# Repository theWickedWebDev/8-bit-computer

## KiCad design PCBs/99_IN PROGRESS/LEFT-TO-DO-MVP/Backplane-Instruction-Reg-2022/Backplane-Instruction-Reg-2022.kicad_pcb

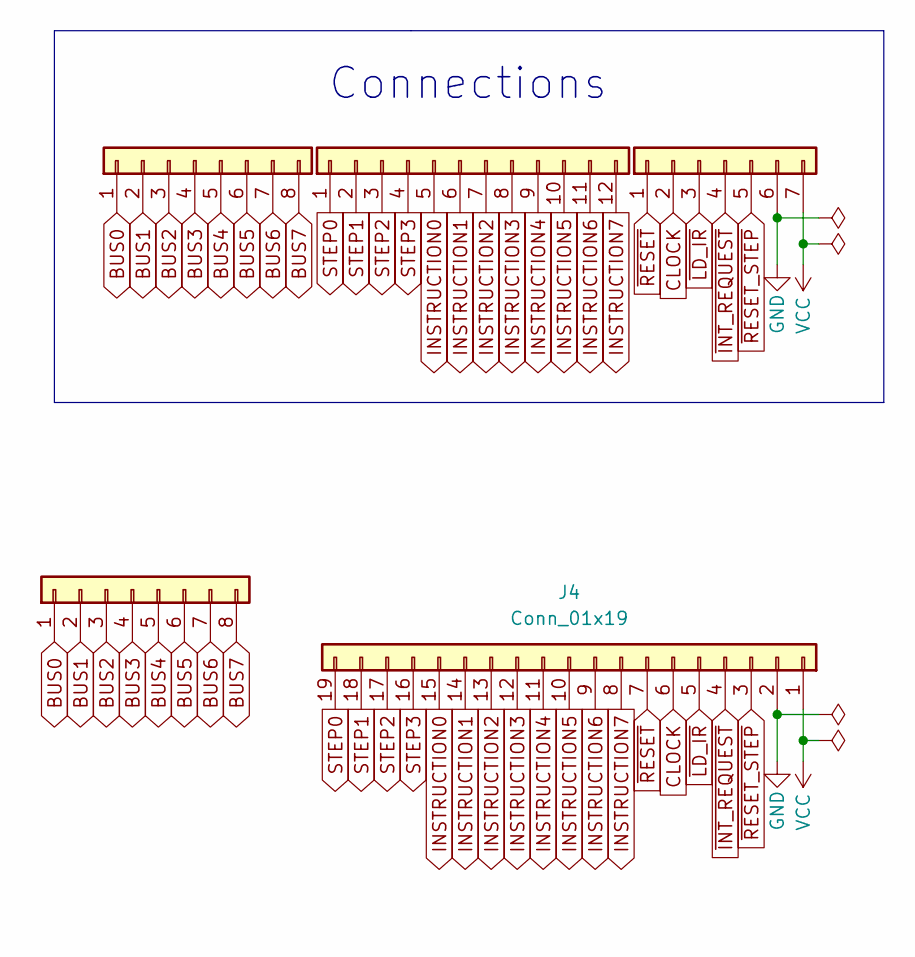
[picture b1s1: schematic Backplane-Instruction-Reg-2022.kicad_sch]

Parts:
J1: Conn_01x08; PinHeader_1x08_P2.54mm_Vertical
J2: Conn_01x08; PinSocket_1x08_P2.54mm_Vertical
J3: Conn_01x12; PinSocket_1x12_P2.54mm_Vertical
J4: Conn_01x19; PinHeader_1x19_P2.54mm_Horizontal
J5: Conn_01x07; PinSocket_1x07_P2.54mm_Vertical

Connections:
BUS0: J1.1, J2.1
BUS1: J1.2, J2.2
BUS2: J1.3, J2.3
BUS3: J1.4, J2.4
BUS4: J1.5, J2.5
BUS5: J1.6, J2.6
BUS6: J1.7, J2.7
BUS7: J1.8, J2.8
CLOCK: J4.6, J5.2
GND: J4.2, J5.6
INSTRUCTION0: J3.5, J4.15
INSTRUCTION1: J3.6, J4.14
INSTRUCTION2: J3.7, J4.13
INSTRUCTION3: J3.8, J4.12
INSTRUCTION4: J3.9, J4.11
INSTRUCTION5: J3.10, J4.10
INSTRUCTION6: J3.11, J4.9
INSTRUCTION7: J3.12, J4.8
STEP0: J3.1, J4.19
STEP1: J3.2, J4.18
STEP2: J3.3, J4.17
STEP3: J3.4, J4.16
VCC: J4.1, J5.7
~INT_REQUEST: J4.4, J5.4
~LD_IR: J4.5, J5.3
~RESET_STEP: J4.3, J5.5
~RESET: J4.7, J5.1

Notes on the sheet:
Connections

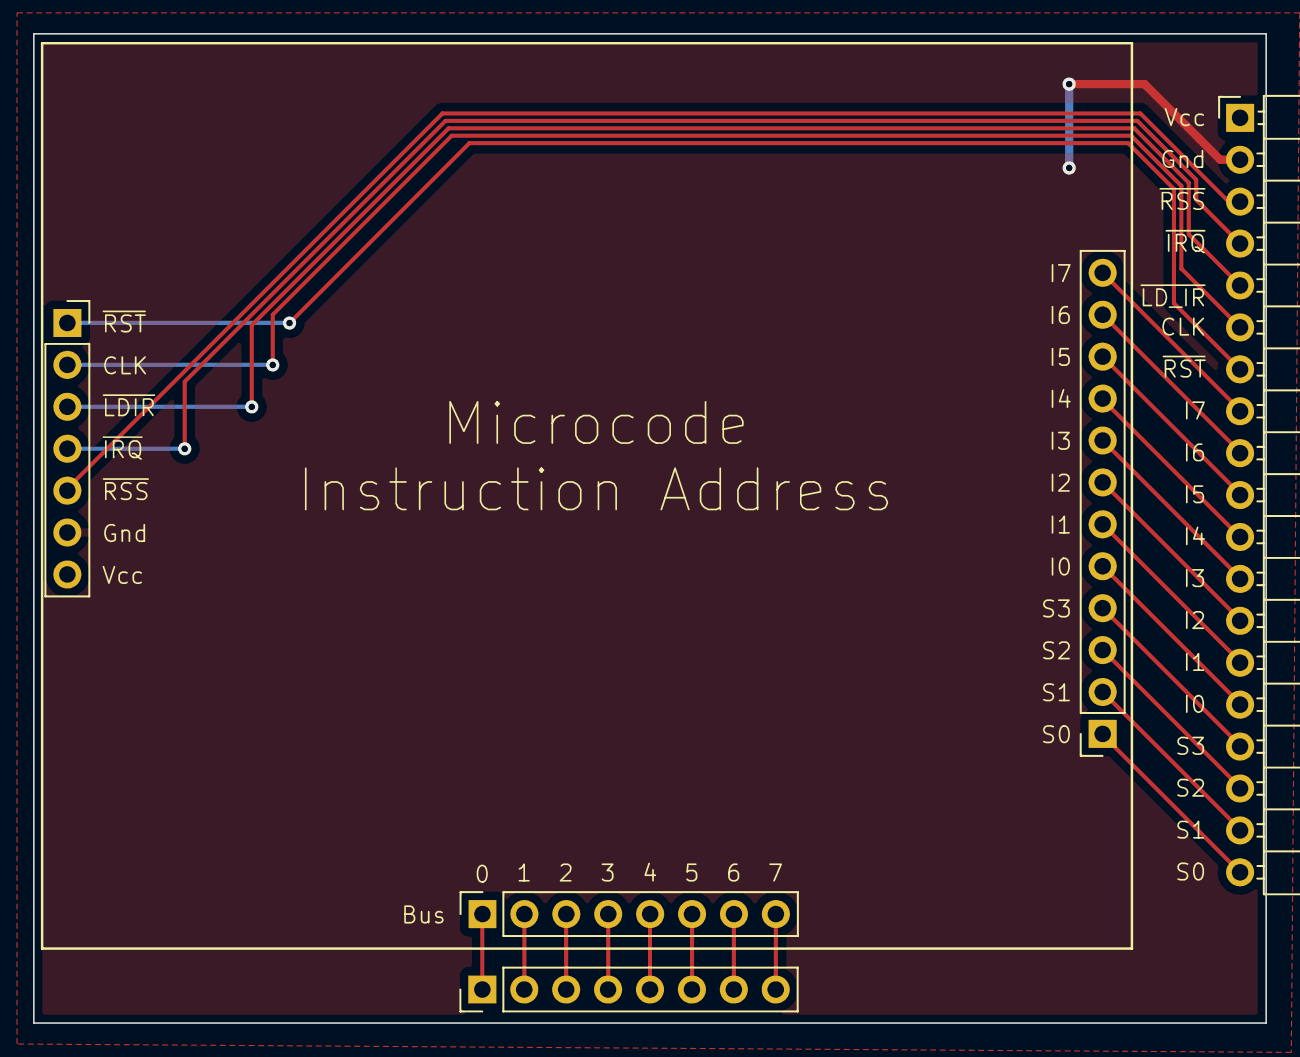
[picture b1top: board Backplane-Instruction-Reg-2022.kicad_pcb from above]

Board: 2 copper layers, 74.7 x 59.9 mm, 5 parts (0 on the bottom side), 27 nets.

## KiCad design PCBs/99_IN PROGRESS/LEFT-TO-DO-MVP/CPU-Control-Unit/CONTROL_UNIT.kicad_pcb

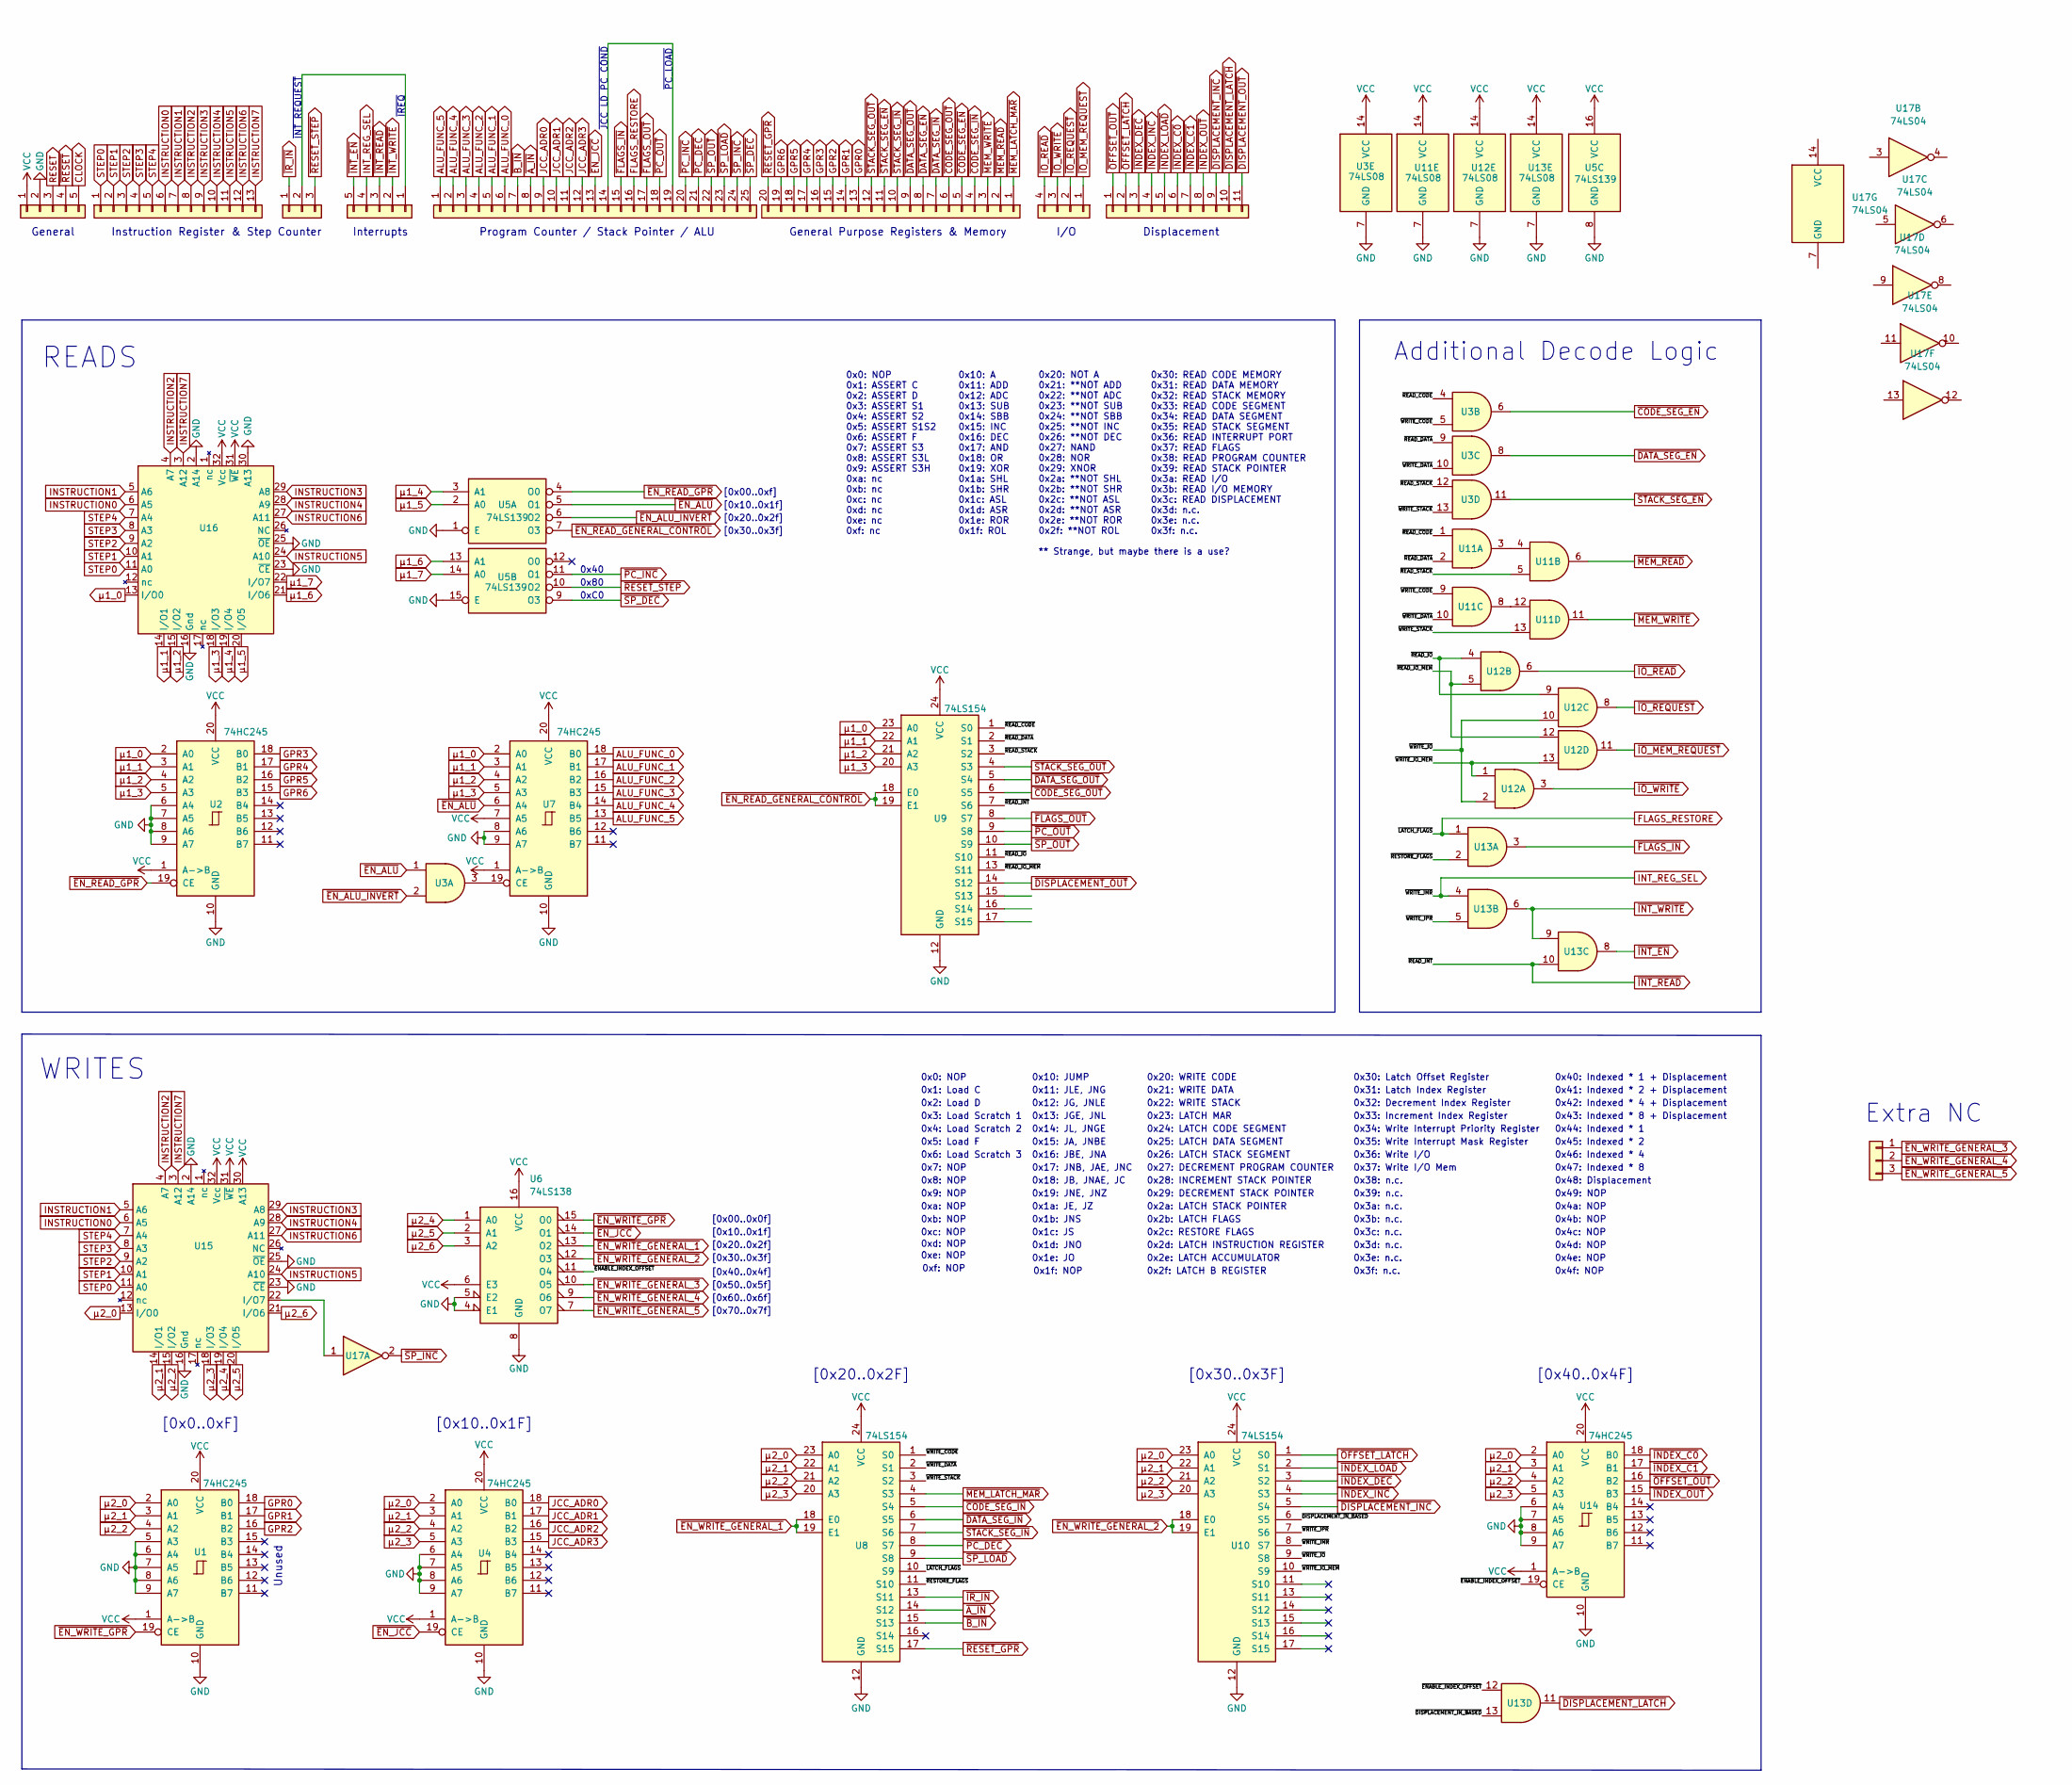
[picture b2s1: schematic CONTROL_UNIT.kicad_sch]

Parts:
J1, J4: Conn_01x05; PinHeader_1x05_P2.54mm_Vertical
J2: Conn_01x13; PinHeader_1x13_P2.54mm_Vertical
J3, J9: Conn_01x03; PinHeader_1x03_P2.54mm_Vertical
J5: Conn_01x25; PinHeader_1x25_P2.54mm_Vertical
J6: Conn_01x20; PinHeader_1x20_P2.54mm_Vertical
J7: Conn_01x04; PinHeader_1x04_P2.54mm_Vertical
J8: Conn_01x10; PinHeader_1x11_P2.54mm_Vertical
U1, U2, U4, U7, U14: 74HC245; SOIC-20W_7.5x12.8mm_P1.27mm
U3, U11, U12, U13: 74LS08; SOIC-14_3.9x8.7mm_P1.27mm
U5: 74LS139; SOIC-16_3.9x9.9mm_P1.27mm
U6: 74LS138; SOIC-16_3.9x9.9mm_P1.27mm
U8, U9, U10: 74LS154; SOIC-24W_7.5x15.4mm_P1.27mm
U15, U16: PLCC32_28_28C256; Socket-PLCC-32
U17: 74LS04

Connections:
/~DISPLACEMENT_IN_BASED: U10.6 (S5), U13.13
/~ENABLE_INDEX_OFFSET: U6.11 (O4), U13.12, U14.19 (CE)
/~READ_CODE: U3.4, U9.1 (S0), U11.1
/~READ_DATA: U3.9, U9.2 (S1), U11.2
/~READ_IO_MEM: U9.13 (S11), U12.5, U12.12
/~READ_IO: U9.11 (S10), U12.4, U12.9
/~READ_STACK: U3.12, U9.3 (S2), U11.5
/~RESTORE_FLAGS: U8.11 (S10), U13.2
/~WRITE_CODE: U3.5, U8.1 (S0), U11.9
/~WRITE_DATA: U3.10, U8.2 (S1), U11.10
/~WRITE_IO_MEM: U10.10 (S9), U12.1, U12.13
/~WRITE_IO: U10.9 (S8), U12.2, U12.10
/~WRITE_IPR: U10.7 (S6), U13.5
/~WRITE_STACK: U3.13, U8.3 (S2), U11.13
ALU_FUNC_0: J5.6, U7.18 (B0)
ALU_FUNC_1: J5.5, U7.17 (B1)
ALU_FUNC_2: J5.4, U7.16 (B2)
ALU_FUNC_3: J5.3, U7.15 (B3)
ALU_FUNC_4: J5.2, U7.14 (B4)
ALU_FUNC_5: J5.1, U7.13 (B5)
CLOCK: J1.5
FLAGS_RESTORE: J5.16, U8.10 (S9), U13.1
GND: J1.2, U1.5 (A3), U1.6 (A4), U1.7 (A5), U1.8 (A6), U1.9 (A7), U1.10 (GND), U2.6 (A4), U2.7 (A5), U2.8 (A6), U2.9 (A7), U2.10 (GND), U3.7 (GND), U4.6 (A4), U4.7 (A5), U4.8 (A6), U4.9 (A7), U4.10 (GND), U5.1 (E), U5.8 (GND), U5.15 (E), U6.4 (E1), U6.5 (E2), U6.8 (GND), U7.8 (A6), U7.9 (A7), U7.10 (GND), U8.12 (GND), U9.12 (GND), U10.12 (GND), U11.7 (GND), U12.7 (GND), U13.7 (GND), U14.6 (A4), U14.7 (A5), U14.8 (A6), U14.9 (A7), U14.10 (GND), U15.2 (A14), U15.16 (Gnd), U15.23 (~CE), U15.25 (~OE), U16.2 (A14), U16.16 (Gnd), U16.23 (~CE), U16.25 (~OE), U16.30 (A13)
GPR0: J6.13, U1.18 (B0)
GPR1: J6.14, U1.17 (B1)
GPR2: J6.15, U1.16 (B2)
GPR3: J6.16, U2.18 (B0)
GPR4: J6.17, U2.17 (B1)
GPR5: J6.18, U2.16 (B2)
GPR6: J6.19, U2.15 (B3)
INSTRUCTION0: J2.6, U15.6 (A5), U16.6 (A5)
INSTRUCTION1: J2.7, U15.5 (A6), U16.5 (A6)
INSTRUCTION2: J2.8, U15.4 (A7), U16.4 (A7)
INSTRUCTION3: J2.9, U15.29 (A8), U16.29 (A8)
INSTRUCTION4: J2.10, U15.28 (A9), U16.28 (A9)
INSTRUCTION5: J2.11, U15.24 (A10), U16.24 (A10)
INSTRUCTION6: J2.12, U15.27 (A11), U16.27 (A11)
INSTRUCTION7: J2.13, U15.3 (A12), U16.3 (A12)
INT_REG_SEL: J4.4, U10.8 (S7), U13.4
JCC_ADR0: J5.9, U4.18 (B0)
JCC_ADR1: J5.10, U4.17 (B1)
JCC_ADR2: J5.11, U4.16 (B2)
JCC_ADR3: J5.12, U4.15 (B3)
unnamed: J3.2, J4.1
unnamed: J5.14, J5.19
unnamed: U3.3, U7.19 (CE)
unnamed: U11.3, U11.4
unnamed: U11.8, U11.12
unnamed: U15.22 (I/O7), U17.1
RESET: J1.3
STEP0: J2.1, U15.11 (A0), U16.11 (A0)
STEP1: J2.2, U15.10 (A1), U16.10 (A1)
STEP2: J2.3, U15.9 (A2), U16.9 (A2)
STEP3: J2.4, U15.8 (A3), U16.8 (A3)
STEP4: J2.5, U15.7 (A4), U16.7 (A4)
VCC: J1.1, U1.1 (A->B), U1.20 (VCC), U2.1 (A->B), U2.20 (VCC), U3.14 (VCC), U4.1 (A->B), U4.20 (VCC), U5.16 (VCC), U6.6 (E3), U6.16 (VCC), U7.1 (A->B), U7.7 (A5), U7.20 (VCC), U8.24 (VCC), U9.24 (VCC), U10.24 (VCC), U11.14 (VCC), U12.14 (VCC), U13.14 (VCC), U14.1 (A->B), U14.20 (VCC), U15.30 (A13), U15.31 (~WE), U15.32 (Vcc), U16.31 (~WE), U16.32 (Vcc)
~A_IN: J5.8, U8.14 (S12)
~B_IN: J5.7, U8.15 (S13)
~CODE_SEG_EN: J6.5, U3.6
~CODE_SEG_IN: J6.4, U8.5 (S4)
~CODE_SEG_OUT: J6.6, U9.6 (S5)
~DATA_SEG_EN: J6.8, U3.8
~DATA_SEG_IN: J6.7, U8.6 (S5)
~DATA_SEG_OUT: J6.9, U9.5 (S4)
~DISPLACEMENT_INC: J8.9, U10.5 (S4)
~DISPLACEMENT_LATCH: J8.10, U13.11
~DISPLACEMENT_OUT: J8.11, U9.14 (S12)
~EN_ALU_INVERT: U3.2, U5.6 (O2)
~EN_ALU: U3.1, U5.5 (O1), U7.6 (A4)
~EN_JCC: J5.13, U4.19 (CE), U6.14 (O1)
~EN_READ_GENERAL_CONTROL: U5.7 (O3), U9.18 (E0), U9.19 (E1)
~EN_READ_GPR: U2.19 (CE), U5.4 (O0)
~EN_WRITE_GENERAL_1: U6.13 (O2), U8.18 (E0), U8.19 (E1)
~EN_WRITE_GENERAL_2: U6.12 (O3), U10.18 (E0), U10.19 (E1)
~EN_WRITE_GENERAL_3: J9.1, U6.10 (O5)
~EN_WRITE_GENERAL_4: J9.2, U6.9 (O6)
~EN_WRITE_GENERAL_5: J9.3, U6.7 (O7)
~EN_WRITE_GPR: U1.19 (CE), U6.15 (O0)
~FLAGS_IN: J5.15, U13.3
~FLAGS_OUT: J5.17, U9.8 (S7)
~INDEX_C0: J8.6, U14.18 (B0)
~INDEX_C1: J8.7, U14.17 (B1)
~INDEX_DEC: J8.3, U10.3 (S2)
~INDEX_INC: J8.4, U10.4 (S3)
~INDEX_LOAD: J8.5, U10.2 (S1)
~INDEX_OUT: J8.8, U14.15 (B3)
~INT_EN: J4.5, U13.8
~INT_READ: J4.3, U9.7 (S6), U13.10
~INT_WRITE: J4.2, U13.6, U13.9
~IO_MEM_REQUEST: J7.1, U12.11
~IO_READ: J7.4, U12.6
~IO_REQUEST: J7.2, U12.8
~IO_WRITE: J7.3, U12.3
~IR_IN: J3.1, U8.13 (S11)
~MEM_LATCH_MAR: J6.1, U8.4 (S3)
~MEM_READ: J6.2, U11.6
~MEM_WRITE: J6.3, U11.11
~OFFSET_LATCH: J8.2, U10.1 (S0)
~OFFSET_OUT: J8.1, U14.16 (B2)
~PC_DEC: J5.21, U8.8 (S7)
~PC_INC: J5.20, U5.11 (O1)
~PC_OUT: J5.18, U9.9 (S8)
~RESET_GPR: J6.20, U8.17 (S15)
~RESET_STEP: J3.3, U5.10 (O2)
~RESET: J1.4
~SP_DEC: J5.25, U5.9 (O3)
~SP_INC: J5.24, U17.2
~SP_LOAD: J5.23, U8.9 (S8)
~SP_OUT: J5.22, U9.10 (S9)
~STACK_SEG_EN: J6.11, U3.11
~STACK_SEG_IN: J6.10, U8.7 (S6)
~STACK_SEG_OUT: J6.12, U9.4 (S3)
μ1_0: U2.2 (A0), U7.2 (A0), U9.23 (A0), U16.13 (I/O0)
μ1_1: U2.3 (A1), U7.3 (A1), U9.22 (A1), U16.14 (I/O1)
μ1_2: U2.4 (A2), U7.4 (A2), U9.21 (A2), U16.15 (I/O2)
μ1_3: U2.5 (A3), U7.5 (A3), U9.20 (A3), U16.18 (I/O3)
μ1_4: U5.3 (A1), U16.19 (I/O4)
μ1_5: U5.2 (A0), U16.20 (I/O5)
μ1_6: U5.13 (A1), U16.21 (I/O6)
μ1_7: U5.14 (A0), U16.22 (I/O7)
μ2_0: U1.2 (A0), U4.2 (A0), U8.23 (A0), U10.23 (A0), U14.2 (A0), U15.13 (I/O0)
μ2_1: U1.3 (A1), U4.3 (A1), U8.22 (A1), U10.22 (A1), U14.3 (A1), U15.14 (I/O1)
μ2_2: U1.4 (A2), U4.4 (A2), U8.21 (A2), U10.21 (A2), U14.4 (A2), U15.15 (I/O2)
μ2_3: U4.5 (A3), U8.20 (A3), U10.20 (A3), U14.5 (A3), U15.18 (I/O3)
μ2_4: U6.1 (A0), U15.19 (I/O4)
μ2_5: U6.2 (A1), U15.20 (I/O5)
μ2_6: U6.3 (A2), U15.21 (I/O6)

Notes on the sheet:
0x35: Write Interrupt Mask Register
Instruction Register
0x13: JGE, JNL
0x4a: NOP
0x3: Load Scratch 1
[0x30..0x3F]
[0x70..0x7f]
0x47: Indexed * 8
[0x20..0x2f]
0x3f: n.c.
0x17: JNB, JAE, JNC
0x6: Load Scratch 3
0xd: NOP
0x4c: NOP
Interrupts
0x12: JG, JNLE
[0x10..0x1f]
0x8: NOP
0x4f: NOP
0x37: Write I/O Mem
0x21: WRITE DATA
0x4b: NOP
[0x30..0x3f]
0x28: INCREMENT STACK POINTER
0x1c: JS
0xf: NOP
~{JCC_LD_PC_COND}
I/O
[0x40..0x4F]
0x3a: n.c.
0x41: Indexed * 2 + Displacement
0x14: JL, JNGE
WRITES
Program Counter / Stack Pointer / ALU
0x2e: LATCH ACCUMULATOR
0x2b: LATCH FLAGS
0x9: NOP
~{IREQ}
0x3e: n.c.
0x7: NOP

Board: 2 copper layers, 25 parts (8 on the bottom side), 122 nets, no tracks yet.

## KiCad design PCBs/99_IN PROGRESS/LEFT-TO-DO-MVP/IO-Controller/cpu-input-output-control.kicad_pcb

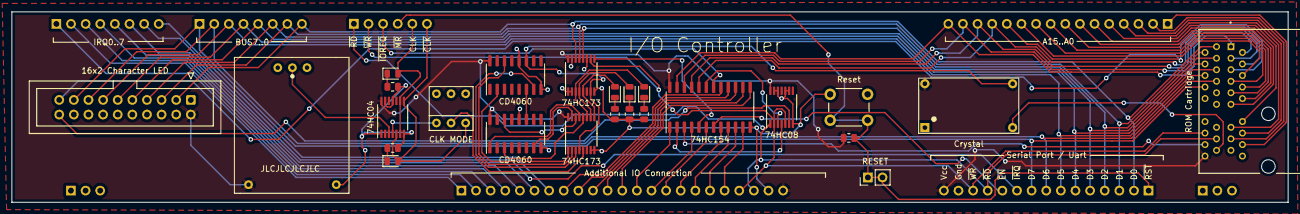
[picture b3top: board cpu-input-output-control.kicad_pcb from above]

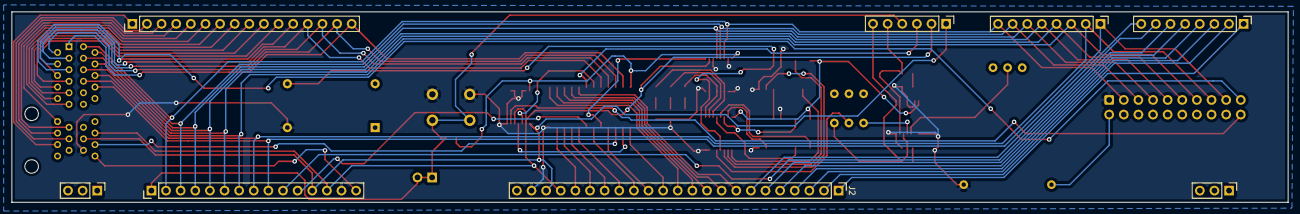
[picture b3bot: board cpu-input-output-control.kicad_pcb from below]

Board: 2 copper layers, 221.7 x 33.1 mm, 33 parts (8 on the bottom side), 78 nets.

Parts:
D1, D2, D3: LED; LED_RED_0805_2012Metric
D4, D5: LED; LED_BLUE_0805_2012Metric
J1: Conn_01x06; PinHeader_1x06_P2.54mm_Vertical
J2: Conn_01x23; PinHeader_1x23_P2.54mm_Vertical
J3: Conn_02x20_Odd_Even; IDC-Header_2x10_P2.54mm_Vertical
J4: Conn_01x02; PinHeader_1x02_P2.54mm_Vertical
J5: Conn_01x15; PinHeader_1x15_P2.54mm_Vertical
J6: Conn_01x16; PinHeader_1x16_P2.54mm_Vertical
J7, J8: Conn_01x03; PinHeader_1x03_P2.54mm_Vertical
J11, J16: Conn_01x08; PinHeader_1x08_P2.54mm_Vertical
J21: PCIE-036-02-X-D-RA; SAMTEC_PCIE-036-02-X-D-RA
R1, R2, R3, R4, R5, R6: R_Small_US; R_0805_2012Metric
SW1: SW_Push; SW_PUSH_6mm
SW2: SW_SPDT; THT-DPDT
U1: 74LS08; TSSOP-14_4.4x5mm_P0.65mm
U2: 74LS04; TSSOP-14_4.4x5mm_P0.65mm
U3: 74LS154; SO-24_5.3x15mm_P1.27mm
U4: debounced-btn; breakout-debounce-btn
U5, U8: CD4060; SOIC-16_3.9x9.9mm_P1.27mm
U6: 74LS173; TSSOP-16_4.4x5mm_P0.65mm
U7: 74LS251; TSSOP-16_4.4x5mm_P0.65mm
Y1: Crystal_GND24; DIP-14-4pin-clock

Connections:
/F0: D3.2 (A), U6.3 (Q0), U7.11 (S0)
/F1: D2.2 (A), U6.4 (Q1), U7.10 (S1)
/F2: D1.2 (A), U6.5 (Q2), U7.9 (S2)
A0: J6.16, J21.A01, U3.23 (A0)
A1: J6.15, J21.A02, U3.22 (A1)
A2: J6.14, J21.A03, U3.21 (A2)
A3: J6.13, J21.A04, U3.20 (A3)
A4: J3.19, J6.12, J21.A05
A5: J6.11, J21.A06
A6: J6.10, J21.A07
A7: J6.9, J21.A08
A8: J6.8, J21.A09
A9: J6.7, J21.A10
A10: J6.6, J21.A11
A11: J6.5, J21.A12
A12: J6.4, J21.A13
A13: J6.3, J21.A14
A14: J6.2, J21.A15
A15: J6.1, J21.A16
BUS0: J3.3, J5.2, J11.8, J21.B01, U6.14 (D0)
BUS1: J3.5, J5.3, J11.7, J21.B02, U6.13 (D1)
BUS2: J3.7, J5.4, J11.6, J21.B03, U6.12 (D2)
BUS3: J3.9, J5.5, J11.5, J21.B04
BUS4: J3.11, J5.6, J11.4, J21.B05
BUS5: J3.13, J5.7, J11.3, J21.B06
BUS6: J3.15, J5.8, J11.2, J21.B07
BUS7: J3.17, J5.9, J11.1, J21.B08
CLOCK: D4.2 (A), J1.5, U2.6, U2.9
CRYSTAL_CLOCK: U5.11 (I), U6.7 (Cp), U7.4 (I0), Y1.3
FREQ1: U5.7 (Q4), U7.3 (I1)
FREQ2: U5.14 (Q8), U7.2 (I2)
FREQ3: U5.2 (Q13), U7.1 (I3)
FREQ4: U7.15 (I4), U8.7 (Q4)
FREQ5: U7.14 (I5), U8.14 (Q8)
FREQ6: U7.13 (I6), U8.1 (Q12)
FREQ7: U7.12 (I7), U8.3 (Q14)
GND: J2.22, J3.1, J5.14, J21.B17, R2.2, R3.2, R4.2, R5.2, R6.2, SW1.1, U1.7 (GND), U1.9, U1.10, U1.12, U1.13, U2.1, U2.7 (GND), U2.11, U2.13, U3.12 (GND), U4.2 (Gnd), U5.8 (GND), U5.12 (RESET), U6.1 (Oe1), U6.2 (Oe2), U6.8 (GND), U6.11 (D3), U6.15 (Mr), U7.7 (~OE), U7.8 (GND), U8.8 (GND), U8.12 (RESET), Y1.2
MANUAL_CLOCK: U2.3, U4.3 (Q)
unnamed: D1.1 (K), R2.1
unnamed: D2.1 (K), R3.1
unnamed: D3.1 (K), R4.1
unnamed: D4.1 (K), R5.1
unnamed: D5.1 (K), R6.1
unnamed: J3.20, U1.6
unnamed: SW2.1 (A), U2.4
unnamed: SW2.3 (C), U7.5 (Y)
unnamed: U1.3, U3.19 (E1)
unnamed: U5.6 (Q7), U8.11 (I)
VCC: J2.23, J3.2, J5.15, J21.B18, R1.2, U1.14 (VCC), U2.14 (VCC), U3.24 (VCC), U4.1 (Vcc), U5.16 (VCC), U6.16 (VCC), U7.16 (VCC), U8.16 (VCC), Y1.4
~CLOCK: D5.2 (A), J1.6, SW2.2 (B), U2.5, U2.8
~IO_REQUEST: J1.3, U3.18 (E0)
~IRQ0: J2.1, J16.1
~IRQ1: J2.2, J16.2
~IRQ2: J2.3, J16.3
~IRQ3: J2.4, J16.4
~IRQ4: J2.5, J16.5
~IRQ5: J2.6, J16.6
~IRQ6: J5.10, J16.7
~IRQ7: J2.7, J16.8
~PORT0_EN: J2.13, U3.1 (S0)
~PORT1_EN: U1.4, U3.2 (S1)
~PORT2_EN: J21.B16, U3.3 (S2)
~PORT3_EN: J2.14, U3.4 (S3)
~PORT4_EN: U3.5 (S4), U6.9 (E1)
~PORT5_EN: J2.15, U3.6 (S5)
~PORT6_EN: J5.11, U3.7 (S6)
~PORT7_EN: J2.16, U3.8 (S7)
~PORT8_EN: J2.17, U3.9 (S8)
~PORT9_EN: J2.18, U3.10 (S9)
~PORT10_EN: J2.19, U3.11 (S10)
~PORT11_EN: J2.12, U3.13 (S11)
~PORT12_EN: J2.11, U3.14 (S12)
~PORT13_EN: J2.10, U3.15 (S13)
~PORT14_EN: J2.9, U3.16 (S14)
~PORT15_EN: J2.8, U3.17 (S15)
~READ: J1.1, J2.21, J5.12, J21.B15, U1.1
~RESET: J1.4, J4.1, J4.2, J5.1, R1.1, SW1.2
~WRITE: J1.2, J2.20, J5.13, J21.B14, U1.2, U1.5, U6.10 (E2)

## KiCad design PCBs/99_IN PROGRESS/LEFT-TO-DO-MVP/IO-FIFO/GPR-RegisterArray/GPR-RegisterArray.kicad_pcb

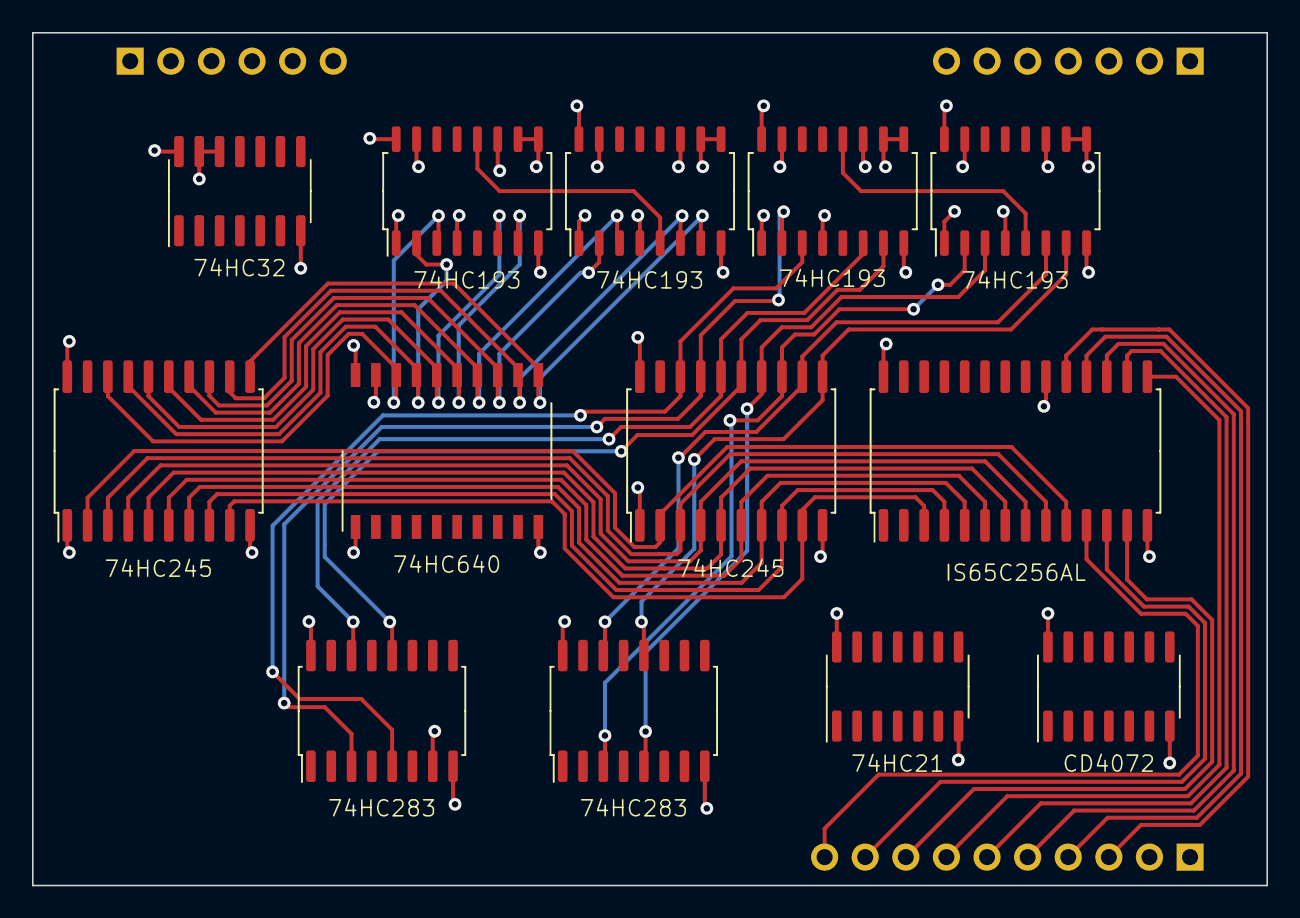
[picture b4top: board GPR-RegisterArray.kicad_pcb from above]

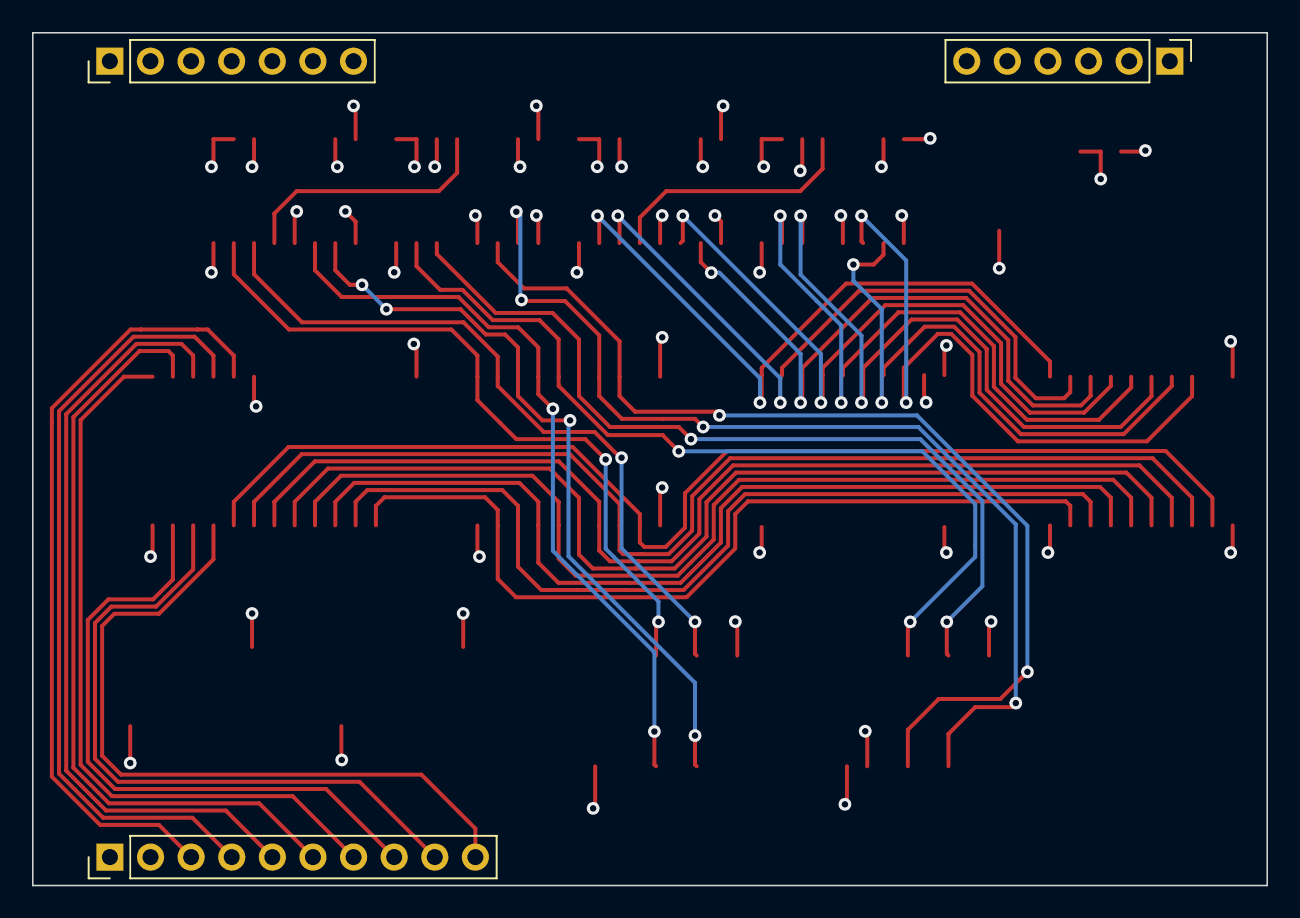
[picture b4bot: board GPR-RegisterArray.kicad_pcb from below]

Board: 4 copper layers, 77.2 x 53.3 mm, 16 parts (3 on the bottom side), 69 nets.

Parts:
J1: Conn_01x10; PinHeader_1x10_P2.54mm_Vertical
J2: Conn_01x06; PinHeader_1x06_P2.54mm_Vertical
J3: Conn_01x07; PinHeader_1x07_P2.54mm_Vertical
U1: 74HC32; SOIC-14_3.9x8.7mm_P1.27mm
U2: IS65C256AL; SOIC-28W_7.5x17.9mm_P1.27mm
U3: 74HC21; SOIC-14_3.9x8.7mm_P1.27mm
U4: CD4072; SOIC-14_3.9x8.7mm_P1.27mm
U7, U8, U10, U11: 74HC193; SOIC-16_4.55x10.3mm_P1.27mm
U9, U12: 74HC245; SOIC-20W_7.5x12.8mm_P1.27mm
U13: 74HC640; SO-20_12.8x7.5mm_P1.27mm
U14, U15: 74HC283; SO-16_5.3x10.2mm_P1.27mm

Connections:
/Subtractor/!B0: U13.2 (A0), U14.6 (B1)
/Subtractor/!B1: U13.3 (A1), U14.2 (B2)
/Subtractor/!B2: U13.4 (A2), U14.15 (B3)
/Subtractor/!B3: U13.5 (A3), U14.11 (B4)
/Subtractor/!B4: U13.6 (A4), U15.6 (B1)
/Subtractor/!B5: U13.7 (A5), U15.2 (B2)
/Subtractor/!B6: U13.8 (A6), U15.15 (B3)
/Subtractor/!B7: U13.9 (A7), U15.11 (B4)
/~READ_EN: U1.6, U2.22 (~OE), U7.5 (UP), U9.19 (CE)
/~WRITE_EN: U1.8, U2.27 (~WE), U10.5 (UP), U12.19 (CE)
A0: U2.10 (A0), U9.2 (A0), U12.2 (A0)
A1: U2.9 (A1), U9.3 (A1), U12.3 (A1)
A2: U2.8 (A2), U9.4 (A2), U12.4 (A2)
A3: U2.7 (A3), U9.5 (A3), U12.5 (A3)
A4: U2.6 (A4), U9.6 (A4), U12.6 (A4)
A5: U2.5 (A5), U9.7 (A5), U12.7 (A5)
A6: U2.4 (A6), U9.8 (A6), U12.8 (A6)
A7: U2.3 (A7), U9.9 (A7), U12.9 (A7)
BANK0: J3.1, U2.25 (A8)
BANK1: J3.2, U2.24 (A9)
BANK2: J3.3, U2.21 (A10)
BANK3: J3.4, U2.23 (A11)
BANK4: J3.5, U2.2 (A12)
BANK5: J3.6, U2.26 (A13)
BANK6: J3.7, U2.1 (A14)
BUS0: J1.10, U2.11 (D0)
BUS1: J1.9, U2.12 (D1)
BUS2: J1.8, U2.13 (D2)
BUS3: J1.7, U2.15 (D3)
BUS4: J1.6, U2.16 (D4)
BUS5: J1.5, U2.17 (D5)
BUS6: J1.4, U2.18 (D6)
BUS7: J1.3, U2.19 (D7)
CLEAR: J2.6, U7.14 (CLR), U8.14 (CLR), U10.14 (CLR), U11.14 (CLR)
COUNT0: U3.1, U4.2, U14.4 (S1)
COUNT1: U3.2, U4.3, U14.1 (S2)
COUNT2: U3.4, U4.4, U14.13 (S3)
COUNT3: U3.5, U4.5, U14.10 (S4)
COUNT4: U3.9, U4.9, U15.4 (S1)
COUNT5: U3.10, U4.10, U15.1 (S2)
COUNT6: U3.12, U4.11, U15.13 (S3)
COUNT7: U3.13, U4.12, U15.10 (S4)
GND: J1.2, U1.7 (GND), U1.12, U1.13, U2.14 (GND), U2.20 (~CS), U3.7 (GND), U4.7 (VSS), U7.1 (B), U7.8 (GND), U7.9 (D), U7.10 (C), U7.15 (A), U8.1 (B), U8.8 (GND), U8.9 (D), U8.10 (C), U8.15 (A), U9.1 (A->B), U9.10 (GND), U10.1 (B), U10.8 (GND), U10.9 (D), U10.10 (C), U10.15 (A), U11.1 (B), U11.8 (GND), U11.9 (D), U11.10 (C), U11.15 (A), U12.1 (A->B), U12.10 (GND), U13.1 (A->B), U13.10 (GND), U13.19 (CE), U14.8 (GND), U15.8 (GND)
unnamed: U1.1, U4.1
unnamed: U1.2, U4.13
unnamed: U7.12 (~CO), U8.5 (UP)
unnamed: U10.12 (~CO), U11.5 (UP)
unnamed: U14.9 (C4), U15.7 (C0)
READ0: U7.3 (QA), U9.18 (B0), U13.18 (B0)
READ1: U7.2 (QB), U9.17 (B1), U13.17 (B1)
READ2: U7.6 (QC), U9.16 (B2), U13.16 (B2)
READ3: U7.7 (QD), U9.15 (B3), U13.15 (B3)
READ4: U8.3 (QA), U9.14 (B4), U13.14 (B4)
READ5: U8.2 (QB), U9.13 (B5), U13.13 (B5)
READ6: U8.6 (QC), U9.12 (B6), U13.12 (B6)
READ7: U8.7 (QD), U9.11 (B7), U13.11 (B7)
VCC: J1.1, U1.14 (VCC), U2.28 (VCC), U3.14 (VCC), U4.14 (VDD), U7.4 (DOWN), U7.11 (~LOAD), U7.16 (VCC), U8.4 (DOWN), U8.11 (~LOAD), U8.16 (VCC), U9.20 (VCC), U10.4 (DOWN), U10.11 (~LOAD), U10.16 (VCC), U11.4 (DOWN), U11.11 (~LOAD), U11.16 (VCC), U12.20 (VCC), U13.20 (VCC), U14.7 (C0), U14.16 (VCC), U15.16 (VCC)
WRITE0: U10.3 (QA), U12.18 (B0), U14.5 (A1)
WRITE1: U10.2 (QB), U12.17 (B1), U14.3 (A2)
WRITE2: U10.6 (QC), U12.16 (B2), U14.14 (A3)
WRITE3: U10.7 (QD), U12.15 (B3), U14.12 (A4)
WRITE4: U11.3 (QA), U12.14 (B4), U15.5 (A1)
WRITE5: U11.2 (QB), U12.13 (B5), U15.3 (A2)
WRITE6: U11.6 (QC), U12.12 (B6), U15.14 (A3)
WRITE7: U11.7 (QD), U12.11 (B7), U15.12 (A4)
~NOT_FULL: J2.4, U1.10
~READ: J2.1, U1.4
~WRITE: J2.2, U1.9
~ZERO: J2.3, U1.3, U1.5
